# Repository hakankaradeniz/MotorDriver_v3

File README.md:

# MotorDriver_v3
MotorDriver_v3 by me

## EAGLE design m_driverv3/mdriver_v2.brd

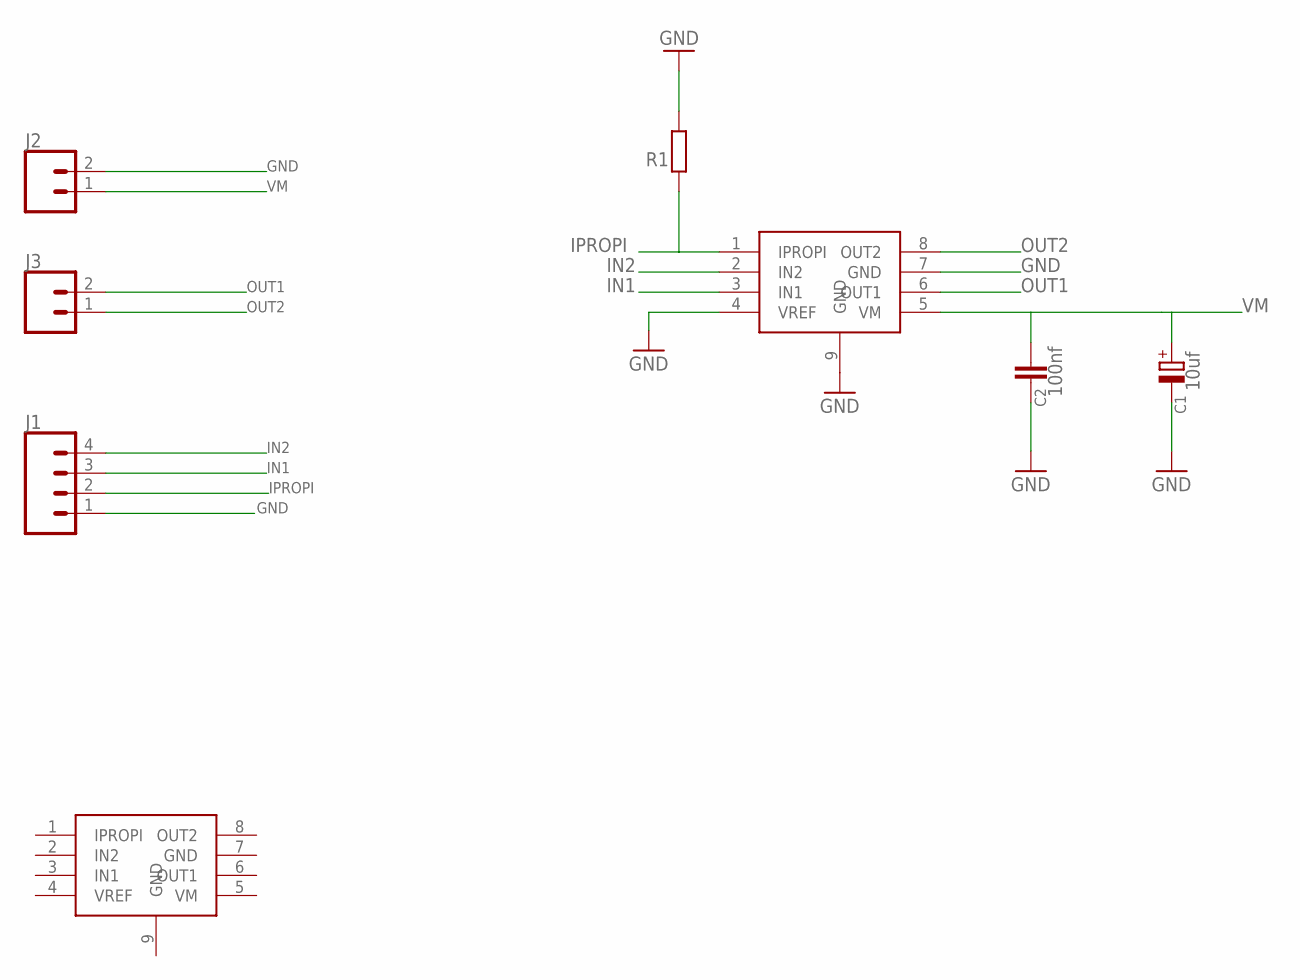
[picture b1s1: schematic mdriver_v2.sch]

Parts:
C1: 10uf; E2,5-6E
C2: 100nf; C025-025X050
J1: CONN_04; 1X04
J2, J3: CONN_02; 1X02
R1: SMK
U$1, U$2: DRV8231A; SOIC127P580X170-9T271X340N

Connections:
GND: C1.-, C2.2, J1.1, J2.2, R1.1, U$1.4 (VREF), U$1.7 (GND), U$1.9 (GND)
IN1: J1.3, U$1.3 (IN1)
IN2: J1.4, U$1.2 (IN2)
IPROPI: J1.2, R1.2, U$1.1 (IPROPI)
OUT1: J3.2, U$1.6 (OUT1)
OUT2: J3.1, U$1.8 (OUT2)
VM: C1.+, C2.1, J2.1, U$1.5 (VM)

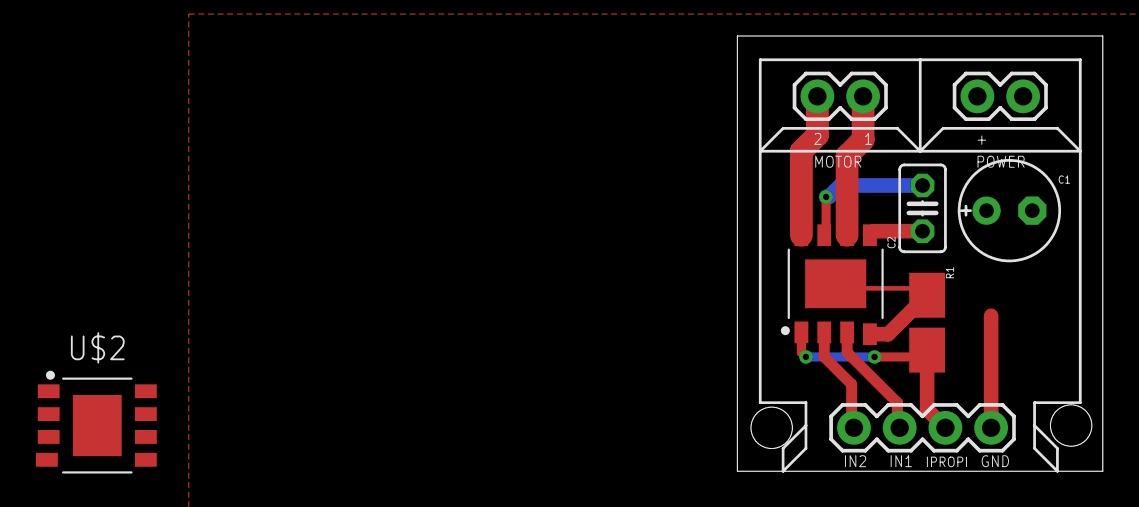
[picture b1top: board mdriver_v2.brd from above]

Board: 2 copper layers, 20.3 x 24.2 mm, 8 parts (0 on the bottom side), 7 nets.

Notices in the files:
parts and their libraries:
SparkFun-Connectors: Licensing: Creative Commons ShareAlike 4.0 International - https://creativecommons.org/licenses/by-sa/4.0
